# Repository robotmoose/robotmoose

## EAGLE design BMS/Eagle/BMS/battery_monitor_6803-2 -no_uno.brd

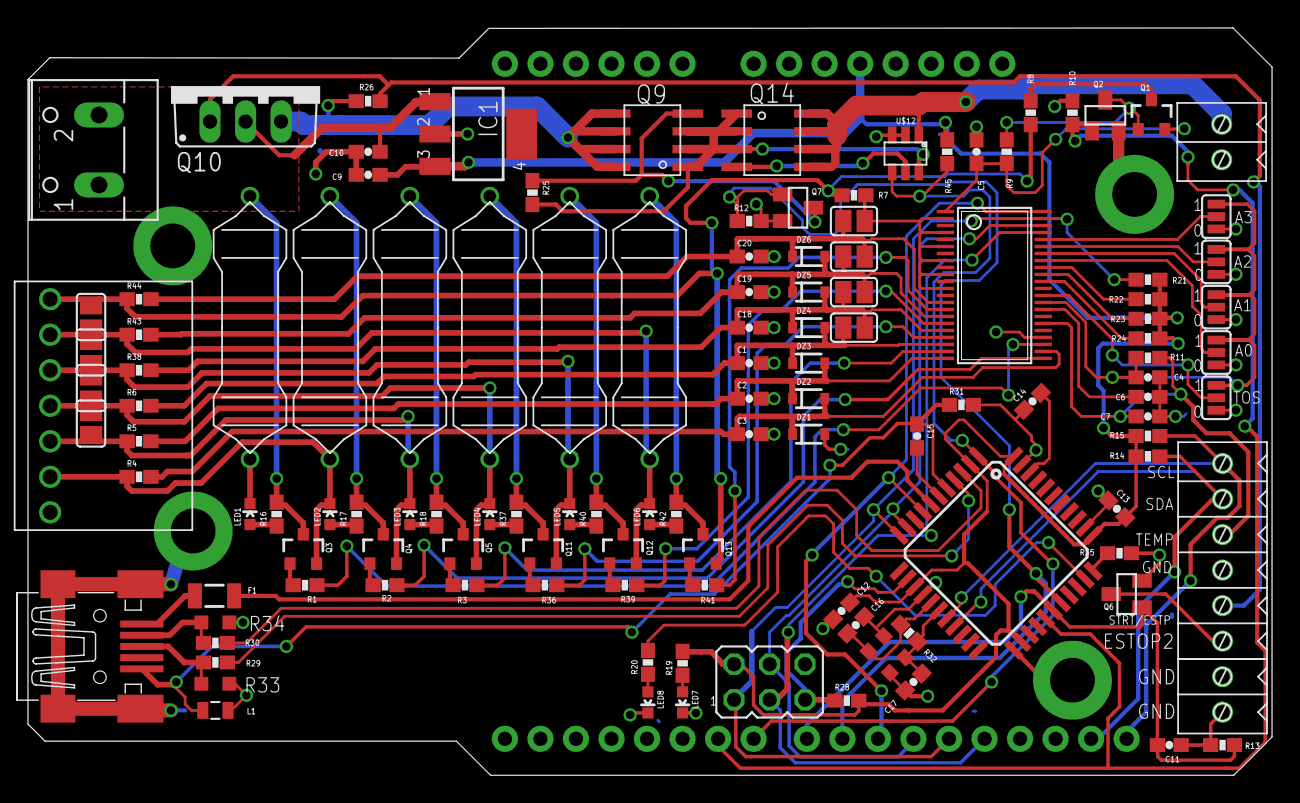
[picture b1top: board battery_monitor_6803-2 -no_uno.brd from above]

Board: 2 copper layers, 88.9 x 53.4 mm, 127 parts (0 on the bottom side), 87 nets.

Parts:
A0, A1, A2, A3: SJ_3
C1, C2, C3, C18, C19, C20: 0.1uF; 0603-CAP
C4, C5, C6, C7, C9, C10, C11, C12, C13, C14, C15: 1uF; 0603-CAP
C16, C17: 20pF; 0603-CAP
DZ1, DZ2, DZ3, DZ4, DZ5, DZ6: PDZ7.5B; SOD-323
F1: PTCSMD; PTC-1206
IC1: MIC2920A-5.0WS; SOT223
J1: ARDUINO_R3_SHIELDNOLABELS; UNO_R3_SHIELD_NOLABELS
JP1: JP3Q
L1: 0805
LED1, LED2, LED3, LED4, LED5, LED6, LED7, LED8: LED-0603
Q1, Q3, Q4, Q5, Q11, Q12, Q13: MOSFET-PCHANNELIRLML2244; SOT23-3
Q2, Q6, Q7: MOSFET-NCHANNELBSS138; SOT23
Q9, Q14: PMOS_AO4435; SOIC8
Q10: IRF9530; TO220BV
R1, R2, R3, R36, R39, R41: 3.3k; 0603-RES
R4, R5, R6, R7, R8, R38, R43, R44: 100; 0603-RES
R9, R10, R12, R13, R14, R15, R21, R25, R26, R28: 4.7k; 0603-RES
R11: 100k; 0603-RES
R16, R17, R18, R19, R20, R37, R40, R42: 470; 0603-RES
R22, R23, R24: 1Meg; 0603-RES
R29, R30: 22ohm; 0603-RES
R31: 0ohm; 0603-RES
R32: 1meg; 0603-RES
R33, R34: VARISTORCN0603; CT/CN0603
R35: 10k; 0603-RES
R45: 470k; 0603-RES
SJ1, SJ2, SJ3, SJ4, SJ5, SJ6, SJ7, SJ8: SJ
TOS: SJ_3
U$1, U$2, U$3, U$8, U$9, U$10: RESISTOR-POWER-3W; RESISTOR-3W
U$4: SCREW_TERMINAL_2
U$5: LTC6803-2; FSOP-44
U$6: ATMEGA32U4TQFP-44; TQFP44
U$7: CRYSTAL_403; CRYSTAL(DFN,LCC)
U$11: JST-XH-7
U$12: LTC4412; SOT-23-6
U$13: SCREW_TERMINAL_8
U$14, U$15, U$16, U$17: MOUNTING_SCREW-3MM
X1: USB-M26FTR; 32005-301
X18: W237-102

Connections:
+5V: C9.1, C12.2, C13.2, IC1.3, J1.5V, JP1.2, R14.2, R15.2, R19.2, R21.2, R22.1, R23.1, R24.1, R28.2, R45.1, U$6.2, U$6.14, U$6.24, U$6.34, U$6.44
+12: C10.1, IC1.1, Q10.D, X18.2
ALL_SYSTEMS_GO: C11.1, J1.D8, Q6.1, R13.2, U$6.28
BATTERY+: Q9.5, Q9.6, Q9.7, Q9.8, Q10.S, R26.2, X18.1
CHARGE: J1.D9, Q7.1, R12.2, U$6.29
CHARGER_CONNECTED: J1.D7, R45.2, U$6.1, U$12.P$4
CHARGER_IN: Q14.5, Q14.6, Q14.7, Q14.8, U$4.P$2, U$12.P$1
D+: R29.2, R33.1, X1.3
D-: R30.2, R34.1, X1.2
E-STOP2: Q6.3, U$13.P$3
GND: A0.3, A1.3, A2.3, A3.3, C1.2, C2.2, C3.2, C4.2, C5.1, C6.1, C7.1, C9.2, C10.2, C11.2, C12.1, C13.1, C14.1, C16.1, C17.2, C18.2, C19.2, C20.2, DZ1.2, IC1.2, J1.GND@0, J1.GND@1, J1.GND@2, JP1.6, L1.1, LED1.C, LED7.C, LED8.C, Q2.2, Q6.2, Q7.2, R10.1, R12.1, R13.1, R31.2, R33.2, R34.2, R35.1, TOS.3, U$1.P$2, U$4.P$1, U$5.26, U$6.15, U$6.23, U$6.35, U$6.43, U$7.CASE, U$7.CASE1, U$11.1, U$12.P$2, U$12.P$3, U$13.P$1, U$13.P$2, U$13.P$5, U$14.P$1, U$15.P$1, U$16.P$1, U$17.P$1, X1.M1, X1.M2, X1.M3, X1.M4
LED: R20.2, U$6.32
MISO: J1.D12, JP1.1, R21.1, U$5.43, U$6.11
MOSI: J1.D11, JP1.4, U$5.42, U$6.10
unnamed: Q7.3, Q9.4, R25.1
unnamed: LED2.C, Q3.2, R4.1, U$2.P$2, U$11.2
unnamed: LED3.C, Q4.2, R5.1, SJ8.2, U$3.P$2, U$11.3
unnamed: LED4.C, Q5.2, R6.1, SJ7.2, SJ8.1, U$8.P$2, U$11.4
unnamed: Q3.3, R16.2, U$1.P$1
unnamed: R2.2, U$5.23
unnamed: Q3.1, R1.1
unnamed: R1.2, U$5.25
unnamed: R3.2, U$5.21
unnamed: Q4.3, R17.2, U$2.P$1
unnamed: Q4.1, R2.1
unnamed: Q5.3, R18.2, U$3.P$1
unnamed: LED1.A, R16.1
unnamed: C1.1, DZ3.1, DZ4.2, R6.2, SJ4.1, U$5.20
unnamed: C3.1, DZ1.1, DZ2.2, R4.2, U$5.24
unnamed: C2.1, DZ2.1, DZ3.2, R5.2, U$5.22
unnamed: R7.2, SJ1.2, U$5.2, U$5.4, U$5.6, U$5.8, U$5.10, U$5.12
unnamed: Q1.3, R8.2
unnamed: C5.2, Q1.2, R9.2, U$5.1
unnamed: Q1.1, Q2.3, R9.1
unnamed: LED7.A, R19.1
unnamed: LED2.A, R17.1
unnamed: LED3.A, R18.1
unnamed: R22.2, U$5.36
unnamed: R23.2, U$5.35
unnamed: R24.2, U$5.34
unnamed: A3.2, U$5.40
unnamed: Q5.1, R3.1
unnamed: A2.2, U$5.39
unnamed: A1.2, U$5.38
unnamed: A0.2, U$5.37
unnamed: TOS.2, U$5.32
unnamed: C6.2, U$5.30
unnamed: LED8.A, R20.1
unnamed: C15.2, U$6.6
unnamed: F1.1, X1.1
unnamed: C14.2, U$6.42
unnamed: R35.2, U$6.33
unnamed: R36.2, U$5.19
unnamed: Q11.1, R36.1
unnamed: Q11.3, R37.2, U$8.P$1
unnamed: LED4.A, R37.1
unnamed: R29.1, U$6.4
unnamed: R30.1, U$6.3
unnamed: LED5.C, Q11.2, R38.1, SJ6.2, SJ7.1, U$9.P$2, U$11.5
unnamed: R39.2, U$5.17
unnamed: Q12.1, R39.1
unnamed: F1.2, U$6.7
unnamed: C17.1, R32.1, U$6.17, U$7.IN
unnamed: C16.2, R32.2, U$6.16, U$7.OUT
unnamed: Q12.3, R40.2, U$9.P$1
unnamed: LED5.A, R40.1
unnamed: C18.1, DZ4.1, DZ5.2, R38.2, SJ3.1, SJ4.2, U$5.18
unnamed: LED6.C, Q12.2, R43.1, SJ5.2, SJ6.1, U$10.P$2, U$11.6
unnamed: R41.2, U$5.15
unnamed: Q13.1, R41.1
unnamed: Q9.1, Q9.2, Q9.3, Q14.1, Q14.2, Q14.3, R25.2, U$12.P$6
unnamed: LED6.A, R42.1
unnamed: C19.1, DZ5.1, DZ6.2, R43.2, SJ2.1, SJ3.2, U$5.16
unnamed: Q13.2, R7.1, R8.1, R44.1, SJ5.1, U$11.7
unnamed: C20.1, DZ6.1, R44.2, SJ1.1, SJ2.2, U$5.14
unnamed: Q14.4, U$12.P$5
unnamed: Q13.3, R42.2, U$10.P$1
PWR: J1.D6, Q2.1, R10.2, U$6.27
RESET: JP1.5, R28.1, U$6.13
SCK: J1.D13, JP1.3, U$5.41, U$6.9
SCL: J1.SCL, R15.1, U$6.18, U$13.P$8
SDA: J1.SDA, R14.1, U$6.19, U$13.P$7
SS: J1.D10, U$5.44, U$6.8
START/E-STOP1: Q10.G, R26.1, U$13.P$4
UGND: C15.1, L1.2, R31.1, U$6.5, X1.5
VREG: A0.1, A1.1, A2.1, A3.1, C4.1, R11.2, TOS.1, U$5.31
VTEMP1: C7.2, R11.1, U$5.28, U$13.P$6

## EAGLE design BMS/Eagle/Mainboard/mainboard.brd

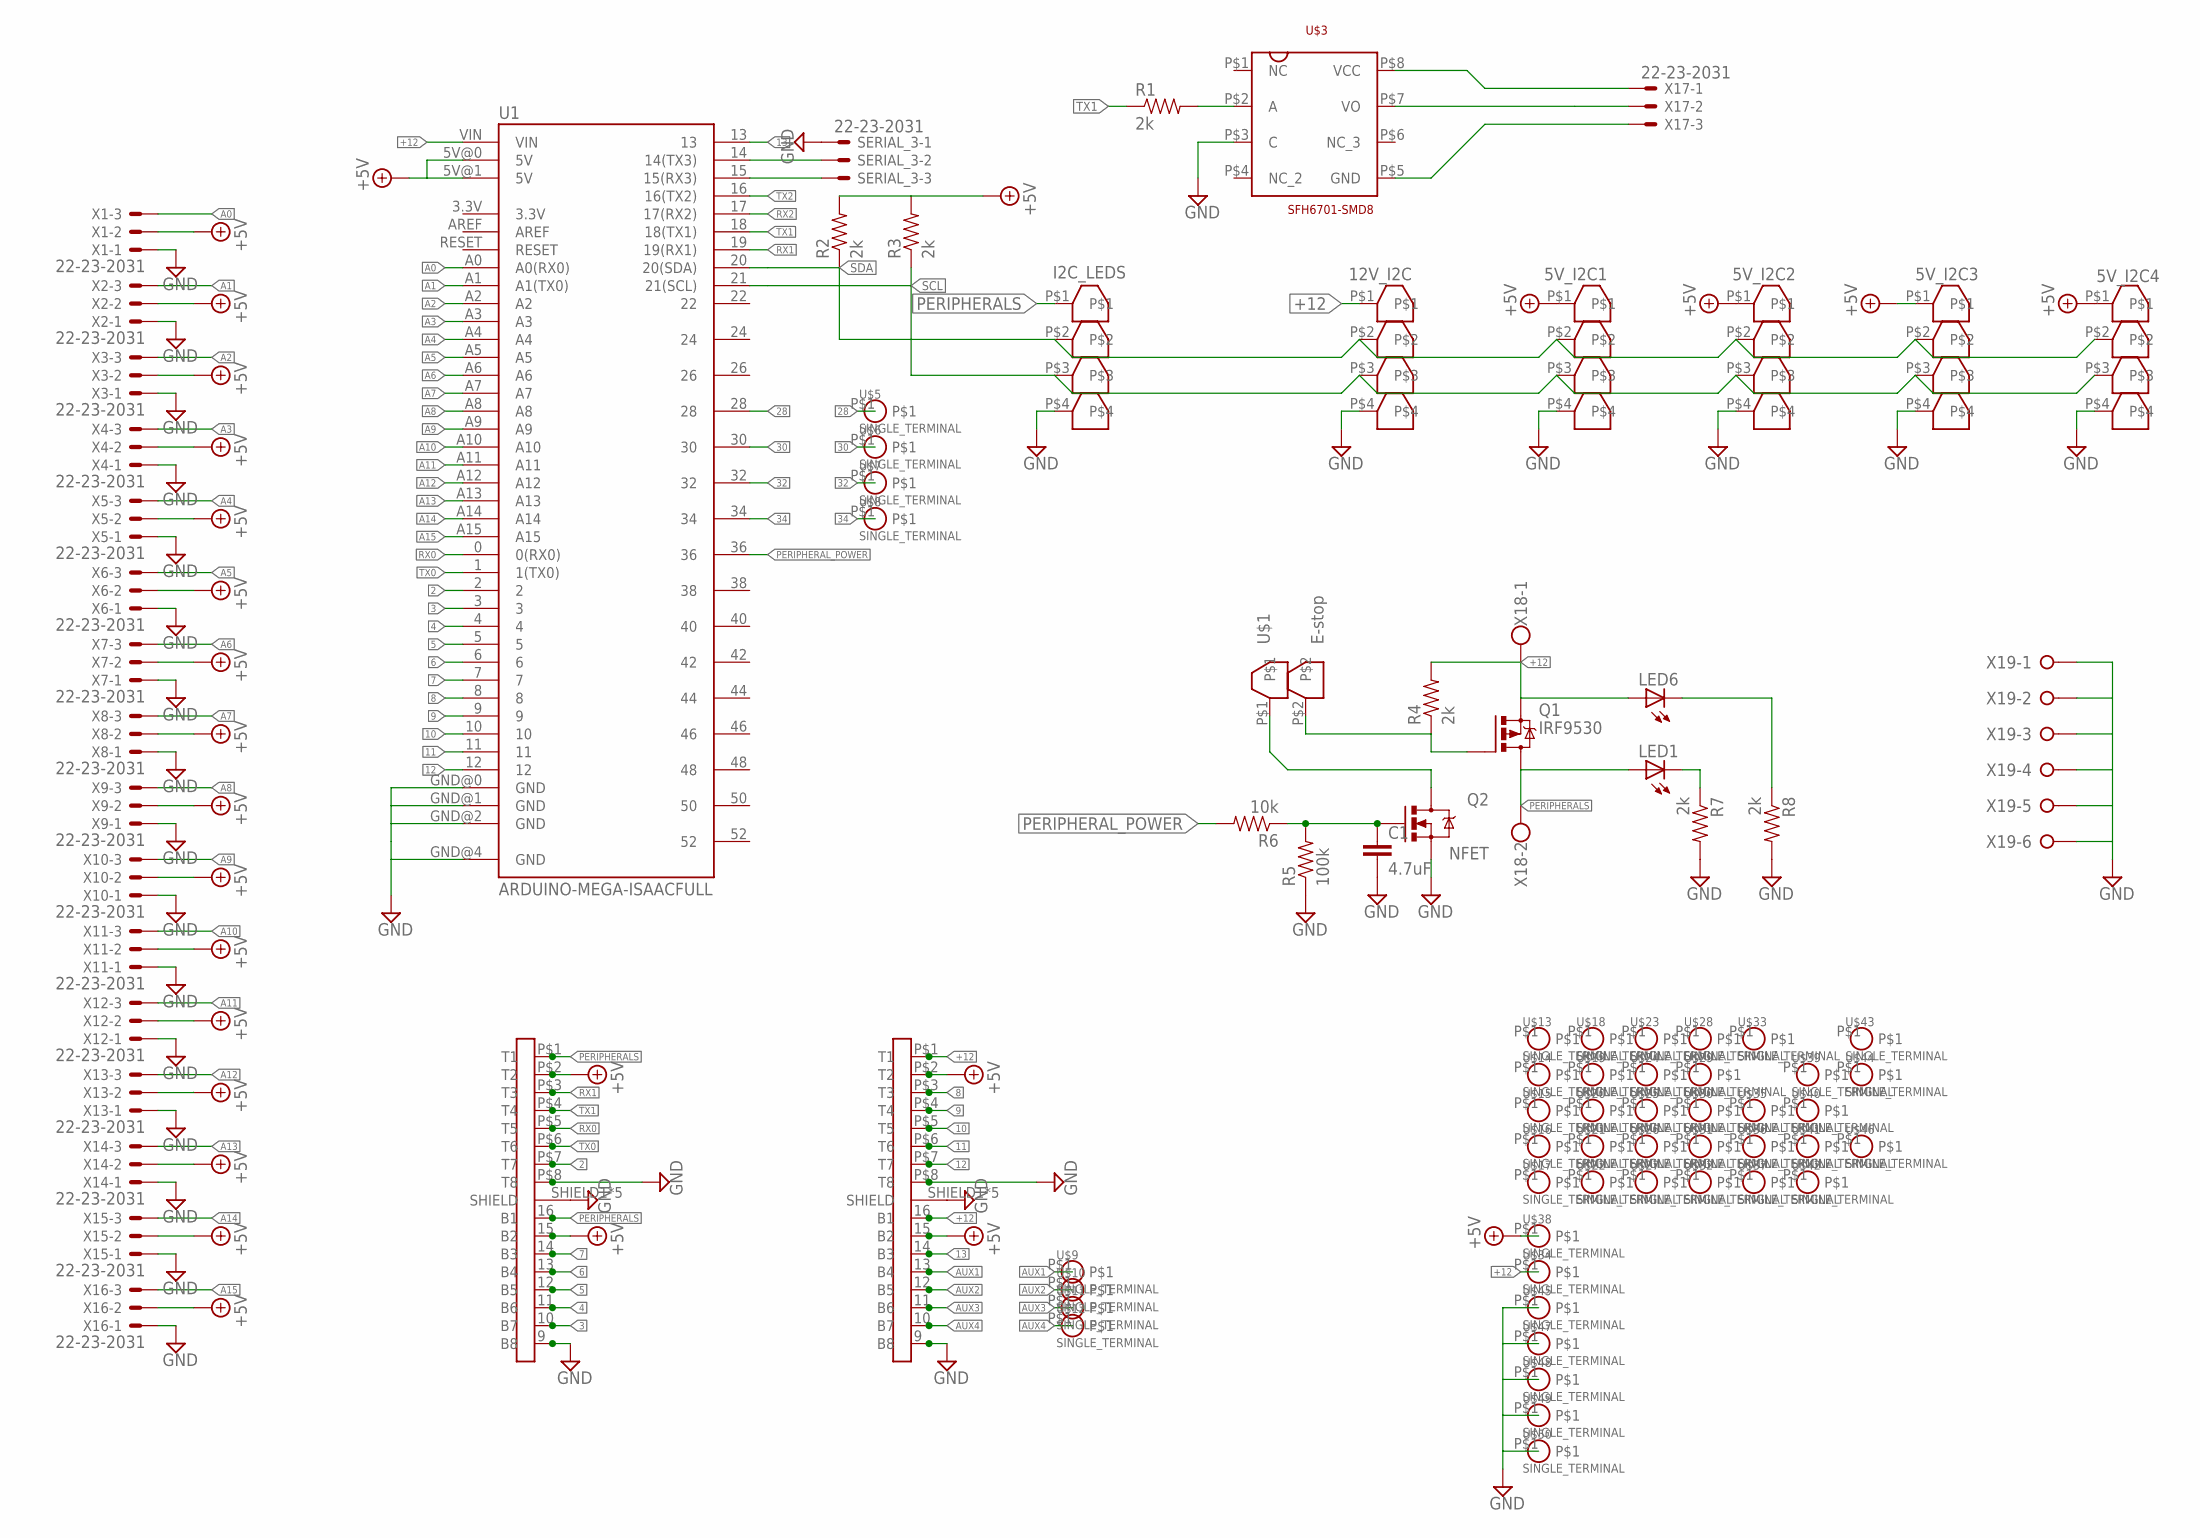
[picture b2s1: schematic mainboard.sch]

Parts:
5V_I2C1, 5V_I2C2, 5V_I2C3, 5V_I2C4, 12V_I2C: SCREW_TERMINAL_4
C1: 4.7uF; C0603
I2C_LEDS: SCREW_TERMINAL_4
LED1, LED6: LED0603; LED-0603
Q1: IRF9530; TO220BV
Q2: NFET; SOT23
R1, R2, R3, R4, R7, R8: 2k; 0603-RES
R5: 100k; 0603-RES
R6: 10k; 0603-RES
SERIAL_3: 22-23-2031; MPN 22-23-2031
U1: ARDUINO-MEGA-ISAACFULL; ARDUINO_MEGA_ISAAC
U$1: E-stop; SCREW_TERMINAL_2
U$2, U$4: RJ45-DUAL-STACKED; RJ45-DUAL-10118096
U$3: SFH6701-SMD8; 8-SMD-GULLWING
U$5, U$6, U$7, U$8, U$9, U$10, U$11, U$12, U$13, U$14, U$15, U$16, U$17, U$18, U$19, U$20, U$21, U$22, U$23, U$24, U$25, U$26, U$27, U$28, U$29, U$30, U$31, U$32, U$33, U$34, U$35, U$36, U$37, U$38, U$39, U$40, U$41, U$42, U$43, U$44, U$45, U$46, U$47, U$48, U$49, U$50: SINGLE_TERMINAL; PLATED_HOLE
X1, X2, X3, X4, X5, X6, X7, X8, X9, X10, X11, X12, X13, X14, X15, X16: 22-23-2031
X17: 22-23-2031; MPN 22-23-2031
X18: W237-102
X19: W237-06P; W237-6P

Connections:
2: U1.2, U$4.P$7 (T7)
3: U1.3, U$4.10 (B7)
4: U1.4, U$4.11 (B6)
5: U1.5, U$4.12 (B5)
6: U1.6, U$4.13 (B4)
7: U1.7, U$4.14 (B3)
8: U1.8, U$2.P$3 (T3)
9: U1.9, U$2.P$4 (T4)
10: U1.10, U$2.P$5 (T5)
11: U1.11, U$2.P$6 (T6)
12: U1.12, U$2.P$7 (T7)
13: U1.13, U$2.14 (B3)
28: U1.28, U$5.P$1
30: U1.30, U$6.P$1
32: U1.32, U$7.P$1
34: U1.34, U$8.P$1
+5V: 5V_I2C1.P$1, 5V_I2C2.P$1, 5V_I2C3.P$1, 5V_I2C4.P$1, R2.2, R3.2, U1.5V@0 (5V), U1.5V@1 (5V), U$2.15 (B2), U$2.P$2 (T2), U$4.15 (B2), U$4.P$2 (T2), U$38.P$1, X1.2, X2.2, X3.2, X4.2, X5.2, X6.2, X7.2, X8.2, X9.2, X10.2, X11.2, X12.2, X13.2, X14.2, X15.2, X16.2
+12: 12V_I2C.P$1, LED6.A, Q1.S, R4.2, U1.VIN, U$2.16 (B1), U$2.P$1 (T1), U$34.P$1, X18.1
A0: U1.A0 (A0(RX0)), X1.3
A1: U1.A1 (A1(TX0)), X2.3
A2: U1.A2, X3.3
A3: U1.A3, X4.3
A4: U1.A4, X5.3
A5: U1.A5, X6.3
A6: U1.A6, X7.3
A7: U1.A7, X8.3
A8: U1.A8, X9.3
A9: U1.A9, X10.3
A10: U1.A10, X11.3
A11: U1.A11, X12.3
A12: U1.A12, X13.3
A13: U1.A13, X14.3
A14: U1.A14, X15.3
A15: U1.A15, X16.3
AUX1: U$2.13 (B4), U$9.P$1
AUX2: U$2.12 (B5), U$10.P$1
AUX3: U$2.11 (B6), U$11.P$1
AUX4: U$2.10 (B7), U$12.P$1
GND: 5V_I2C1.P$4, 5V_I2C2.P$4, 5V_I2C3.P$4, 5V_I2C4.P$4, 12V_I2C.P$4, C1.2, I2C_LEDS.P$4, Q2.2 (S), R5.1, R7.2, R8.2, SERIAL_3.1, U1.GND@0 (GND), U1.GND@1 (GND), U1.GND@2 (GND), U1.GND@4 (GND), U$2.9 (B8), U$2.P$8 (T8), U$2.SHIELD1 (SHIELD), U$2.SHIELD2 (SHIELD), U$2.SHIELD3 (SHIELD), U$2.SHIELD4 (SHIELD), U$2.SHIELD5 (SHIELD), U$3.P$3 (C), U$4.9 (B8), U$4.P$8 (T8), U$4.SHIELD1 (SHIELD), U$4.SHIELD2 (SHIELD), U$4.SHIELD3 (SHIELD), U$4.SHIELD4 (SHIELD), U$4.SHIELD5 (SHIELD), U$45.P$1, U$47.P$1, U$48.P$1, U$49.P$1, U$50.P$1, X1.1, X2.1, X3.1, X4.1, X5.1, X6.1, X7.1, X8.1, X9.1, X10.1, X11.1, X12.1, X13.1, X14.1, X15.1, X16.1, X19.1, X19.2, X19.3, X19.4, X19.5, X19.6
N: Q1.G, R4.1, U$1.P$2
N1: C1.1, Q2.1 (G), R5.2, R6.1
unnamed: U$3.P$8 (VCC), X17.1
unnamed: R1.2, U$3.P$2 (A)
unnamed: U$3.P$7 (VO), X17.2
unnamed: U$3.P$5 (GND), X17.3
unnamed: SERIAL_3.3, U1.15 (15(RX3))
unnamed: SERIAL_3.2, U1.14 (14(TX3))
unnamed: Q2.3 (D), U$1.P$1
unnamed: LED1.C, R7.1
unnamed: LED6.C, R8.1
PERIPHERALS: I2C_LEDS.P$1, LED1.A, Q1.D, U$4.16 (B1), U$4.P$1 (T1), X18.2
PERIPHERAL_POWER: R6.2, U1.36
RX0: U1.0 (0(RX0)), U$4.P$5 (T5)
RX1: U1.19 (19(RX1)), U$4.P$3 (T3)
RX2: U1.17 (17(RX2))
SCL: 5V_I2C1.P$3, 5V_I2C2.P$3, 5V_I2C3.P$3, 5V_I2C4.P$3, 12V_I2C.P$3, I2C_LEDS.P$3, R3.1, U1.21 (21(SCL))
SDA: 5V_I2C1.P$2, 5V_I2C2.P$2, 5V_I2C3.P$2, 5V_I2C4.P$2, 12V_I2C.P$2, I2C_LEDS.P$2, R2.1, U1.20 (20(SDA))
TX0: U1.1 (1(TX0)), U$4.P$6 (T6)
TX1: R1.1, U1.18 (18(TX1)), U$4.P$4 (T4)
TX2: U1.16 (16(TX2))

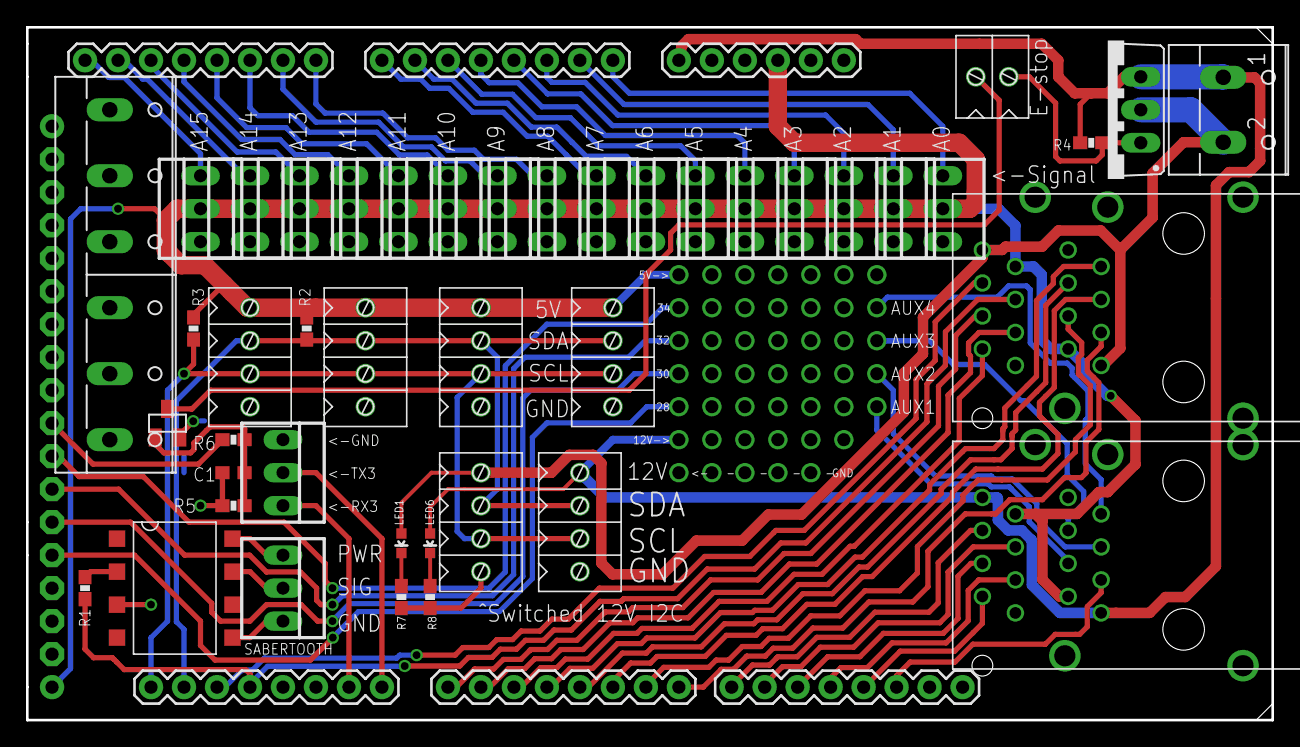
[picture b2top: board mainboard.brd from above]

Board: 2 copper layers, 95.9 x 53.3 mm, 90 parts (0 on the bottom side), 58 nets.

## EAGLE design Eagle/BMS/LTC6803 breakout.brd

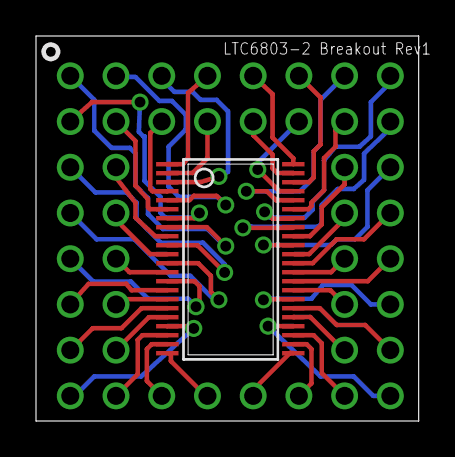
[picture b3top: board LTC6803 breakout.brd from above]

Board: 2 copper layers, 21.3 x 21.4 mm, 45 parts (0 on the bottom side), 44 nets.

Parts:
A0, A1, A2, A3: SINGLE_TERMINAL; PLATED_HOLE
C1, C2, C3, C4, C5, C6, C7, C8, C9, C10, C11, C15: SINGLE_TERMINAL; PLATED_HOLE
CSBI: SINGLE_TERMINAL; PLATED_HOLE
GPIO1, GPIO2: SINGLE_TERMINAL; PLATED_HOLE
NC, NC1: SINGLE_TERMINAL; PLATED_HOLE
S1, S2, S3, S4, S5, S6, S7, S8, S9, S10, S11, S12: SINGLE_TERMINAL; PLATED_HOLE
SCKI: SINGLE_TERMINAL; PLATED_HOLE
SDI: SINGLE_TERMINAL; PLATED_HOLE
SDO: SINGLE_TERMINAL; PLATED_HOLE
TOS: SINGLE_TERMINAL; PLATED_HOLE
U$21: LTC6803-2; FSOP-44
V+: SINGLE_TERMINAL; PLATED_HOLE
V-: SINGLE_TERMINAL; PLATED_HOLE
VREF: SINGLE_TERMINAL; PLATED_HOLE
VREG: SINGLE_TERMINAL; PLATED_HOLE
VTEMP1, VTEMP2: SINGLE_TERMINAL; PLATED_HOLE
WDTB: SINGLE_TERMINAL; PLATED_HOLE

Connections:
1: U$21.1, V+.P$1
2: C15.P$1, U$21.2
3: S12.P$1, U$21.3
4: C11.P$1, U$21.4
5: S11.P$1, U$21.5
6: C10.P$1, U$21.6
7: S10.P$1, U$21.7
8: C9.P$1, U$21.8
9: S9.P$1, U$21.9
10: C8.P$1, U$21.10
11: S8.P$1, U$21.11
12: C7.P$1, U$21.12
13: S7.P$1, U$21.13
14: C6.P$1, U$21.14
15: S6.P$1, U$21.15
16: C5.P$1, U$21.16
17: S5.P$1, U$21.17
18: C4.P$1, U$21.18
19: S4.P$1, U$21.19
20: C3.P$1, U$21.20
21: S3.P$1, U$21.21
22: C2.P$1, U$21.22
23: S2.P$1, U$21.23
24: C1.P$1, U$21.24
25: S1.P$1, U$21.25
26: U$21.26, V-.P$1
27: NC.P$1, U$21.27
28: U$21.28, VTEMP1.P$1
29: U$21.29, VTEMP2.P$1
30: U$21.30, VREF.P$1
31: U$21.31, VREG.P$1
32: TOS.P$1, U$21.32
33: NC1.P$1, U$21.33
34: U$21.34, WDTB.P$1
35: GPIO1.P$1, U$21.35
36: GPIO2.P$1, U$21.36
37: A0.P$1, U$21.37
38: A1.P$1, U$21.38
39: A2.P$1, U$21.39
40: A3.P$1, U$21.40
41: SCKI.P$1, U$21.41
42: SDI.P$1, U$21.42
43: SDO.P$1, U$21.43
44: CSBI.P$1, U$21.44

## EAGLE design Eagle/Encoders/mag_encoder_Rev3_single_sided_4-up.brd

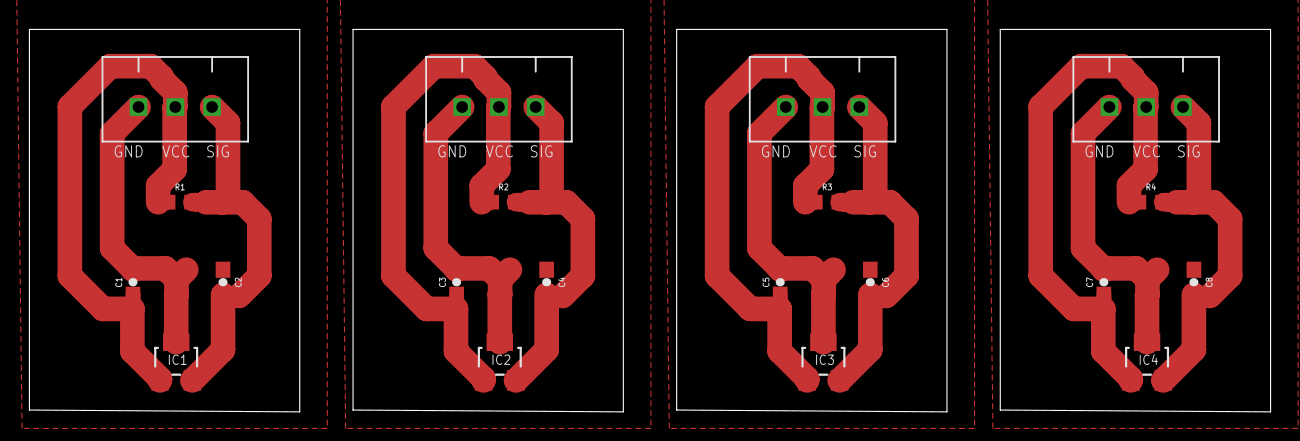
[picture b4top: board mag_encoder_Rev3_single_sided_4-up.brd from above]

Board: 1 copper layer, 84.4 x 26.0 mm, 20 parts (0 on the bottom side), 12 nets.

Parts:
C1, C3, C5, C7: 100nF; 0603-CAP
C2, C4, C6, C8: 4.7nF; 0603-CAP
IC1, IC2, IC3, IC4: A1203LH; SOT23-W
R1, R2, R3, R4: 10k; 0603
U$1, U$2, U$3, U$4: 3_PIN_JST-XH

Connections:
GND: C1.2, C2.2, IC1.3, U$1.P$3
GND1: C3.2, C4.2, IC2.3, U$2.P$3
GND2: C5.2, C6.2, IC3.3, U$3.P$3
GND3: C7.2, C8.2, IC4.3, U$4.P$3
SIG: C2.1, IC1.2, R1.1, U$1.P$1
SIG1: C4.1, IC2.2, R2.1, U$2.P$1
SIG2: C6.1, IC3.2, R3.1, U$3.P$1
SIG3: C8.1, IC4.2, R4.1, U$4.P$1
VCC: C1.1, IC1.1, R1.2, U$1.P$2
VCC1: C3.1, IC2.1, R2.2, U$2.P$2
VCC2: C5.1, IC3.1, R3.2, U$3.P$2
VCC3: C7.1, IC4.1, R4.2, U$4.P$2

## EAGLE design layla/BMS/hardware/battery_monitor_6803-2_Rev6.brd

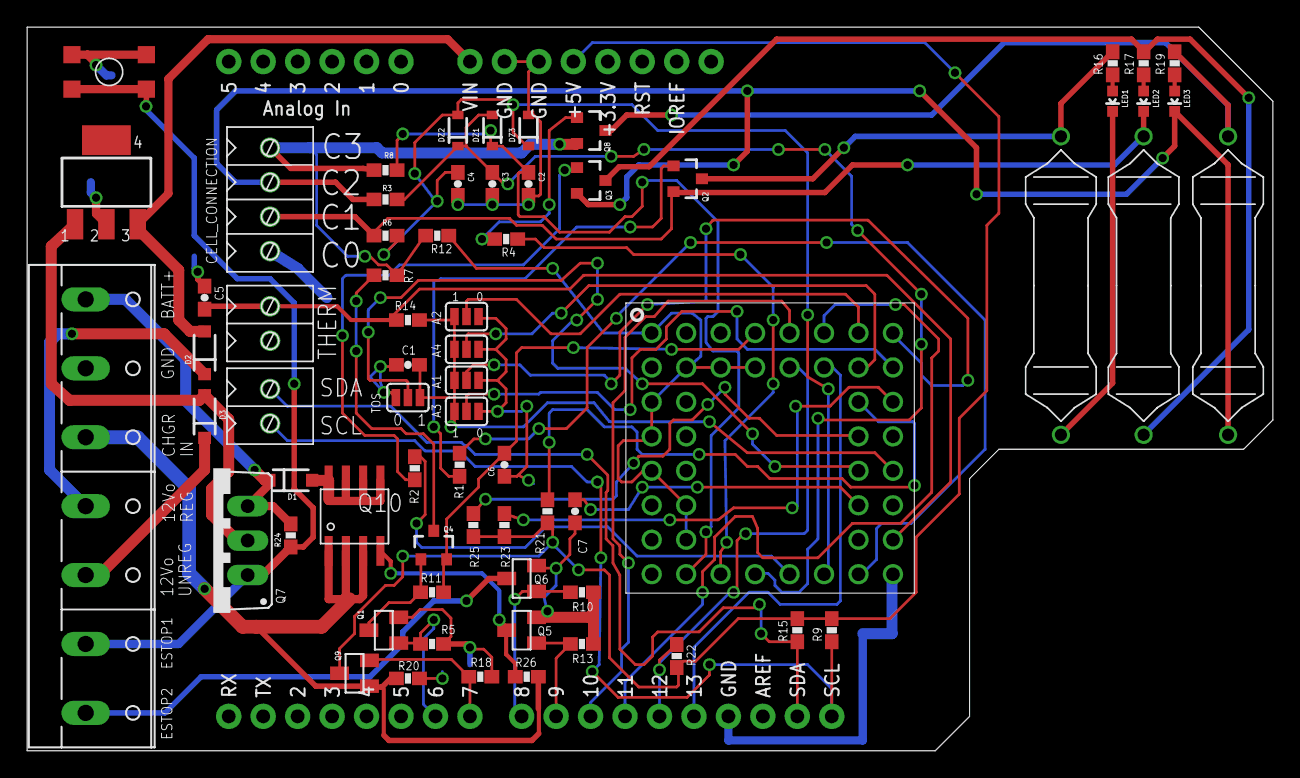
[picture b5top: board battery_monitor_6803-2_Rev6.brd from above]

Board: 2 copper layers, 91.8 x 53.3 mm, 68 parts (0 on the bottom side), 55 nets.

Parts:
A1, A2, A3, A4: SJ_3
C1, C5, C6, C7: 1uF; 0603-CAP
C2, C3, C4: 0.1uF; 0603-CAP
CELL_CONNECTION: SCREW_TERMINAL_4
D1, D2, D3: SMD26PL-TP; SOD-123
DZ1, DZ2, DZ3: PDZ7.5B; SOD-323@1
I2C: SCREW_TERMINAL_2
IC1: MIC2920A-12WS; SOT223
LED1, LED2, LED3: LED-0603
Q1, Q5, Q6, Q9: MOSFET-NCHANNELBSS138; SOT23
Q2, Q3, Q4, Q8: MOSFET-PCHANNELIRLML2244; SOT23-3@1
Q7: IRF9530; TO220BV
Q10: PMOS_AO4435; SOIC8
R1, R2, R4: 3.3k; 0603-RES
R3, R6, R7, R8, R12: 100; 0603-RES
R5, R9, R10, R11, R13, R15, R18, R20, R22, R26: 4.7k; 0603-RES
R14: 100k; 0603-RES
R16, R17, R19: 470; 0603-RES
R21, R23, R24, R25: 1Meg; 0603-RES
THERM: SCREW_TERMINAL_2
TOS: SJ_3
U$1, U$3, U$5: RESISTOR-POWER-3W; RESISTOR-3W
U$2: TACTILE-SWITCH-7914G; 7914G
U$4: LTC6803; LTC6803_BREAKOUT
U$6: ARDUINO_R3_SHIELD; UNO_R3_SHIELD
X1: W237-07P; W237-7P

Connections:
12VREG: D2.A, IC1.3, U$6.VIN
12VUNREG: D3.A, IC1.1, Q7.D
+5: Q9.3, R9.2, R15.2, R21.1, R22.2, R23.1, R25.1, U$6.5V
A0: A3.2, U$4.AO
A1: A1.2, U$4.A1
A2: A4.2, U$4.A2
A3: A2.2, U$4.A3
ALL_SYSTEMS_GO: Q6.1, R10.2, U$6.D8
BATTERY+: D1.C, Q7.S, R24.2, X1.1
C1: C4.1, DZ2.2, DZ3.1, R6.2, U$4.C1
C2: C3.1, DZ1.2, DZ2.1, R3.2, U$4.C2
C3: C2.1, DZ1.1, R8.2, U$4.C3
C12: R12.2, U$4.C4, U$4.C5, U$4.C6, U$4.C7, U$4.C8, U$4.C9, U$4.C10, U$4.C11, U$4.C12
CHARGE: Q5.1, R13.2, U$6.D9
CHARGER_CONNECTED: Q9.2, R18.2, U$6.D7
CHARGER_IN: Q9.1, Q10.1, Q10.2, Q10.3, R20.2, R26.2, X1.3
ESTOP1: Q7.G, R24.1, U$2.3, U$2.4, X1.6
ESTOP2: Q6.3, X1.7
GND: A1.3, A2.3, A3.3, A4.3, C1.2, C2.2, C3.2, C4.2, C5.1, C6.1, C7.1, CELL_CONNECTION.P$4, DZ3.2, IC1.2, LED1.C, Q1.2, Q5.2, Q6.2, R5.1, R10.1, R13.1, R18.1, R20.1, THERM.P$2, TOS.3, U$1.P$2, U$2.1, U$2.2, U$4.V-, U$6.GND@0, U$6.GND@1, U$6.GND@2, X1.2
GPIO1: R23.2, U$4.GPIO1
GPIO2: R21.2, U$4.GPIO2
MISO: R22.1, U$4.SDO, U$6.D12
MOSI: U$4.SDI, U$6.D11
unnamed: Q5.3, Q10.4, R26.1
unnamed: CELL_CONNECTION.P$3, LED2.C, Q2.2, R6.1, U$3.P$2
unnamed: CELL_CONNECTION.P$2, LED3.C, Q3.2, R3.1, U$5.P$2
unnamed: CELL_CONNECTION.P$1, Q8.2, R7.1, R8.1, R12.1
unnamed: Q2.3, R16.2, U$1.P$1
unnamed: Q2.1, R1.1
unnamed: D1.A, Q10.5, Q10.6, Q10.7, Q10.8
unnamed: Q3.3, R17.2, U$3.P$1
unnamed: Q3.1, R2.1
unnamed: Q8.3, R19.2, U$5.P$1
unnamed: LED1.A, R16.1
unnamed: D2.C, X1.4
unnamed: D3.C, X1.5
unnamed: Q4.3, R7.2
unnamed: Q1.3, Q4.1, R11.1
unnamed: LED2.A, R17.1
unnamed: LED3.A, R19.1
unnamed: Q8.1, R4.1
PWR: Q1.1, R5.2, U$6.D6
S1: R1.2, U$4.S1
S2: R2.2, U$4.S2
S3: R4.2, U$4.S3
SCK: U$4.SCKI, U$6.D13
SCL: I2C.P$2, R9.1, U$6.SCL
SDA: I2C.P$1, R15.1, U$6.SDA
SS: U$4.CSBI, U$6.D10
TOS: TOS.2, U$4.TOS
V+: C6.2, Q4.2, R11.2, U$4.V+
VREF: C7.2, U$4.VREF
VREG: A1.1, A2.1, A3.1, A4.1, C1.1, R14.2, TOS.1, U$4.VREG
VTEMP1: C5.2, R14.1, THERM.P$1, U$4.VTEMP1
WDTB: R25.2, U$4.WDTB

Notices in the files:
parts and their libraries:
SparkFun-DiscreteSemi: Licensing: CC v3.0 Share-Alike You are welcome to use this library for commercial purposes.
SparkFun-PowerIC: Licensing: Creative Commons ShareAlike 4.0 International - https://creativecommons.org/licenses/by-sa/4.0
